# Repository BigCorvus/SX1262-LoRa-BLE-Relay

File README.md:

# SX1262-LoRa-BLE-Relay

These are multipurpose dev boards for the Semtech SX1262 chipset. EBYTE or CDSNET or whatever their name is sell multiple versions of RF modules based on this new LoRa chip on Aliexpress. One of its main advantages is the low RX current draw of about 5ma, which is that of the previous versions cut in half.  

This project can be used as a Relay between some BLE device and other LoRa nodes to implement a simple off-grid communicator or some day, as soon as LoRaWAN drivers for the SX1262 exist, it can connect to TTN. Probably the most interesting application: this device is planned to be used as hardware for the Meshtastic project https://github.com/meshtastic/Meshtastic-device  

Discussion: https://meshtastic.discourse.group/t/building-for-nrf52-boards/457/120  

These PCBs are designed for the SPI-versions of the LORA modules only (E22-900M30S which is the 1W version and E22-900M22S which transmits at 160mW max). Both operate in the 868 and 915Mhz band.  The MCU module is a cheap YJ-18010 by Holyiot which has an nRF52840, a ceramic antenna and low frequency crystal on board. The same module is also produced by Waveshare. It runs a Feather-nRF52840 bootloader and has roughly the same pinout, at least for UART, SPI and I2C. A tiny 160x80 IPS screen based on the ST7735 chipset and 3 buttons are provided for basic data visualisation and interfacing.  
When turned off the fuel gauge draws about 25-65µA. While turned on and in receive mode with the backlight off the 30dbm version draws about 18mA. The Backlight is additional 10mA depending on the current limiting resistor and PWM duty cycle. The smaller version draws only 9ma with bluetooth connected and in receive mode!! While transmitting the 30dbm version pulls about 1,2A from the battery!
Note that the 30dbm version of the board needs an extra 5V boost converter, which is a G5177C.  

A simple Arduino test sketch demonstrates the most important functions and can be used for communication already. It will be improved in the future.  

Update: v1.1 of the 30dbm as well as the 22dbm version is out. It has a simple slide switch and uses clickier buttons (LS12T2 from digikey). There's also a JST-SH 1mm connector for GPS modules and a high-side switch (generic SOT23 P-channel mosfet) controlled from P1.00 on the bigger board. LED2 has been moved to P1.10 and the LEDs rearranged. The boost converter is now controlled from P0.05 on the bigger board.

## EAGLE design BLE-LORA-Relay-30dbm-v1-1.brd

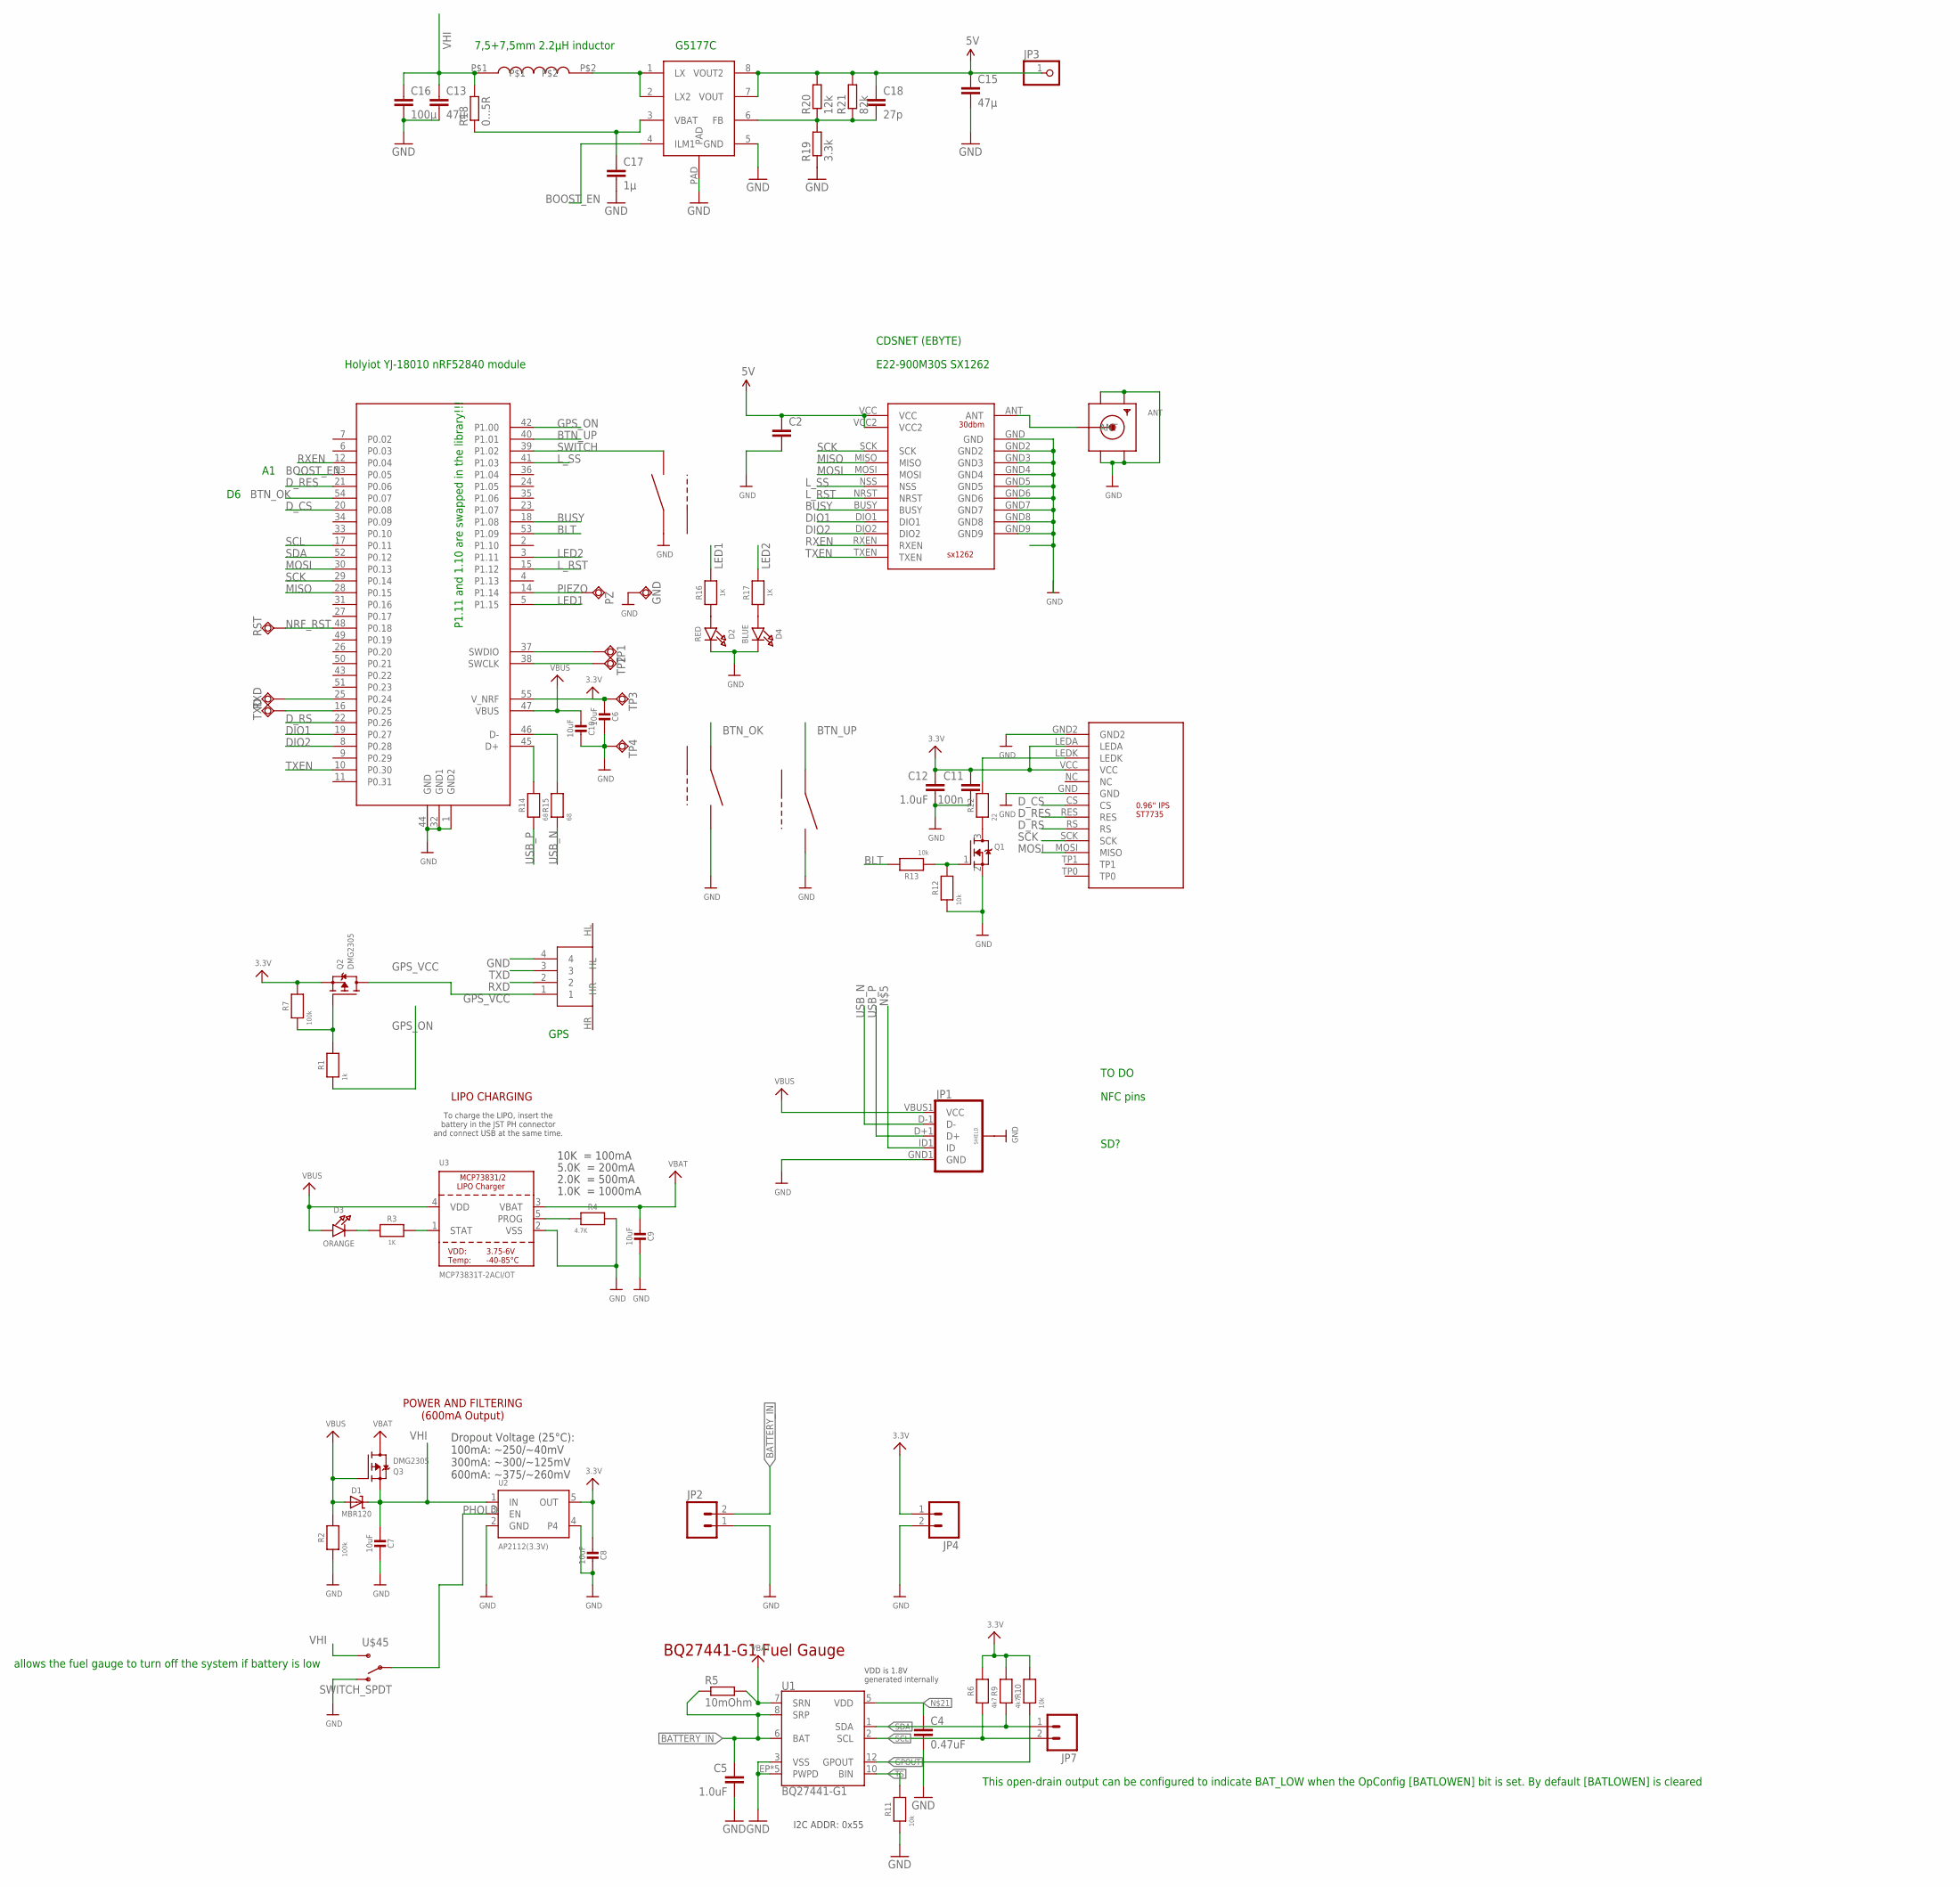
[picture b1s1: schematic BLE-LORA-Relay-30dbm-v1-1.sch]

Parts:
ANT: SMACONNECTOR_EDGE; SMA_EDGELAUNCH
C2: C-EUC1206; C1206
C4: 0.47uF; 0603-CAP
C5, C12: 1.0uF; 0603-CAP
C6, C7, C8, C9, C10: 10uF; 0805-NO
C11: 100n; 0603-CAP
C13, C15: 47µ; C0805
C16: 100µ; C1206
C17: 1µ; C0603
C18: 27p; C0603
D1: MBR120; SOD-123
D2: RED; CHIPLED_0805_NOOUTLINE
D3: ORANGE; CHIPLED_0805_NOOUTLINE
D4: BLUE; CHIPLED_0805_NOOUTLINE
DWN, DWN1, DWN2: LS12T2
GND: TPSQTP13R; TP13R
JP1: USB_MICROB_PLUGCONN-11752; USB-B-MICRO-SMD_V03
JP2, JP4, JP7: M02PTH; 1X02
JP3: PINHD-1X1; 1X01
PZ: TPSQTP13R; TP13R
Q1: MOSFET-NREFLOW; SOT23
Q2, Q3: DMG2305; SOT23-R
R1: 1k; 0603-NO
R2, R7: 100k; 0603-NO
R3, R16, R17: 1K; 0603-NO
R4: 4.7K; 0603-NO
R5: 10mOhm; R0805
R6, R9: 4k7; 0603-NO
R10, R11, R12, R13: 10k; 0603-NO
R14, R15: 68; 0603-NO
R18: 0...5R; R0603
R19: 3.3k; R0603
R20: 12k; R0603
R21: 82k; R0603
R22: 22; 0603-NO
RST: TPSQTP13R; TP13R
RXD: TPSQTP13R; TP13R
TP1, TP2, TP3, TP4: TPSQTP13R; TP13R
TXD: TPSQTP13R; TP13R
U1: BQ27441-G1; PDSO-N12
U2: AP2112(3.3V); SOT23-5
U3: MCP73831T-2ACI/OT; SOT23-5
U$14: NRF52840; NRF52840MOD
U$15: SX1262-30DBM
U$16: 0.96_IPS
U$17: JST-SH-3
U$35: 7.5MM-COIL; 7.5MM_COIL
U$41: G5177C; SO-08
U$45: SWITCH_SPDT; KPS-1290

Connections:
3.3V: C6.2, C8.2, C11.1, C12.1, JP4.1, Q2.2 (S), R6.2, R7.2, R9.2, R10.2, TP3.TP, U2.5 (OUT), U$14.55 (V_NRF), U$16.LEDA, U$16.VCC
5V: C2.1, C15.1, C18.1, JP3.1, R20.2, R21.2, U$15.VCC, U$15.VCC2, U$41.7 (VOUT), U$41.8 (VOUT2)
BATTERY_IN: C5.1, JP2.2, R5.1, U1.6 (BAT), U1.8 (SRP)
BLT: R13.2, U$14.53 (P1.09)
BOOST_EN: U$14.13 (P0.05), U$41.4 (ILM1)
BTN_OK: DWN.2, U$14.54 (P0.07)
BTN_UP: DWN1.2, U$14.40 (P1.01)
BUSY: U$14.18 (P1.08), U$15.BUSY
DIO1: U$14.19 (P0.27), U$15.DIO1
DIO2: U$14.8 (P0.28), U$15.DIO2
D_CS: U$14.20 (P0.08), U$16.CS
D_RES: U$14.21 (P0.06), U$16.RES
D_RS: U$14.22 (P0.26), U$16.RS
FB: C18.2, R19.2, R20.1, R21.1, U$41.6 (FB)
GND: ANT.GND@1 (GND4), ANT.GND@2 (GND3), ANT.GND@3 (GND2), ANT.GND@4 (GND1), C2.2, C4.2, C5.2, C6.1, C7.1, C8.1, C9.1, C10.1, C11.2, C12.2, C13.2, C15.2, C16.2, C17.2, D2.C, D4.C, DWN.1, DWN1.1, DWN2.2, GND.TP, JP1.GND1 (GND), JP1.SHIELD1 (SHIELD), JP1.SHIELD2 (SHIELD), JP1.SHIELD3 (SHIELD), JP2.1, JP4.2, Q1.2 (S), R2.1, R4.2, R11.1, R12.1, R19.1, TP4.TP, U1.3 (VSS), U1.EP (PWPD), U1.EP1 (PWPD), U1.EP2 (PWPD), U1.EP3 (PWPD), U1.EP4 (PWPD), U2.2 (GND), U2.4, U3.2 (VSS), U$14.1 (GND2), U$14.32 (GND1), U$14.44 (GND), U$15.GND, U$15.GND2, U$15.GND3, U$15.GND4, U$15.GND5, U$15.GND6, U$15.GND7, U$15.GND8, U$15.GND9, U$16.GND, U$16.GND2, U$17.4, U$41.5 (GND), U$41.PAD, U$45.O
GPOUT: R10.1, U1.12 (GPOUT)
GPS_ON: R1.1, U$14.42 (P1.00)
GPS_VCC: Q2.3 (D), U$17.1
LED1: R16.2, U$14.5 (P1.15)
LED2: R17.2, U$14.3 (P1.11)
L_RST: U$14.15 (P1.12), U$15.NRST
L_SS: U$14.41 (P1.03), U$15.NSS
MISO: U$14.28 (P0.15), U$15.MISO
MOSI: U$14.30 (P0.13), U$15.MOSI, U$16.MOSI (MISO)
unnamed: D3.C, R3.1
unnamed: Q1.1 (G), R12.2, R13.1
unnamed: ANT.P (ANT), U$15.ANT
unnamed: R22.2, U$16.LEDK
unnamed: R14.2, U$14.45 (D+)
unnamed: R15.2, U$14.46 (D-)
unnamed: Q2.1 (G), R1.2, R7.1
unnamed: R3.2, U3.1 (STAT)
unnamed: R4.1, U3.5 (PROG)
unnamed: D2.A, R16.1
unnamed: D4.A, R17.1
unnamed: Q1.3 (D), R22.1
unnamed: C17.1, R18.1, U$41.3 (VBAT)
unnamed: U$35.P$2, U$41.1 (LX), U$41.2 (LX2)
unnamed: C4.1, U1.5 (VDD)
NRF_RST: RST.TP, U$14.48 (P0.18)
PHOLD: U2.3 (EN), U$45.P
PIEZO: PZ.TP, U$14.14 (P1.14)
RXD: RXD.TP, U$14.25 (P0.24), U$17.2
RXEN: U$14.12 (P0.04), U$15.RXEN
SCK: U$14.29 (P0.14), U$15.SCK, U$16.SCK
SCL: JP7.2, R6.1, U1.2 (SCL), U$14.17 (P0.11)
SDA: JP7.1, R9.1, U1.1 (SDA), U$14.52 (P0.12)
SWCLK: TP2.TP, U$14.38 (SWCLK)
SWDIO: TP1.TP, U$14.37 (SWDIO)
SWITCH: DWN2.1, U$14.39 (P1.02)
TS: R11.2, U1.10 (BIN)
TXD: TXD.TP, U$14.16 (P0.25), U$17.3
TXEN: U$14.10 (P0.30), U$15.TXEN
USB_N: JP1.D-1 (D-), R15.1
USB_P: JP1.D+1 (D+), R14.1
VBAT: C9.2, Q3.3 (D), R5.2, U1.7 (SRN), U3.3 (VBAT)
VBUS: C10.2, D1.A, D3.A, JP1.VBUS1 (VCC), Q3.1 (G), R2.2, U3.4 (VDD), U$14.47 (VBUS)
VHI: C7.2, C13.1, C16.1, D1.C, Q3.2 (S), R18.2, U2.1 (IN), U$35.P$1, U$45.S

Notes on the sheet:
POWER AND FILTERING (600mA Output)
Dropout Voltage (25°C): 100mA: ~250/~40mV 300mA: ~300/~125mV 600mA: ~375/~260mV
10K = 100mA
5.0K = 200mA
2.0K = 500mA
1.0K = 1000mA
LIPO CHARGING
To charge the LIPO, insert the battery in the JST PH connector and connect USB at the same time.
BQ27441-G1 Fuel Gauge
VDD is 1.8V generated internally
I2C ADDR: 0x55
Holyiot YJ-18010 nRF52840 module
E22-900M30S SX1262
CDSNET (EBYTE)
7,5+7,5mm 2.2µH inductor
G5177C
P1.11 and 1.10 are swapped in the library!!!
GPS
allows the fuel gauge to turn off the system if battery is low
This open-drain output can be configured to indicate BAT_LOW when the OpConfig [BATLOWEN] bit is set. By default [BATLOWEN] is cleared
TO DO
NFC pins
SD?

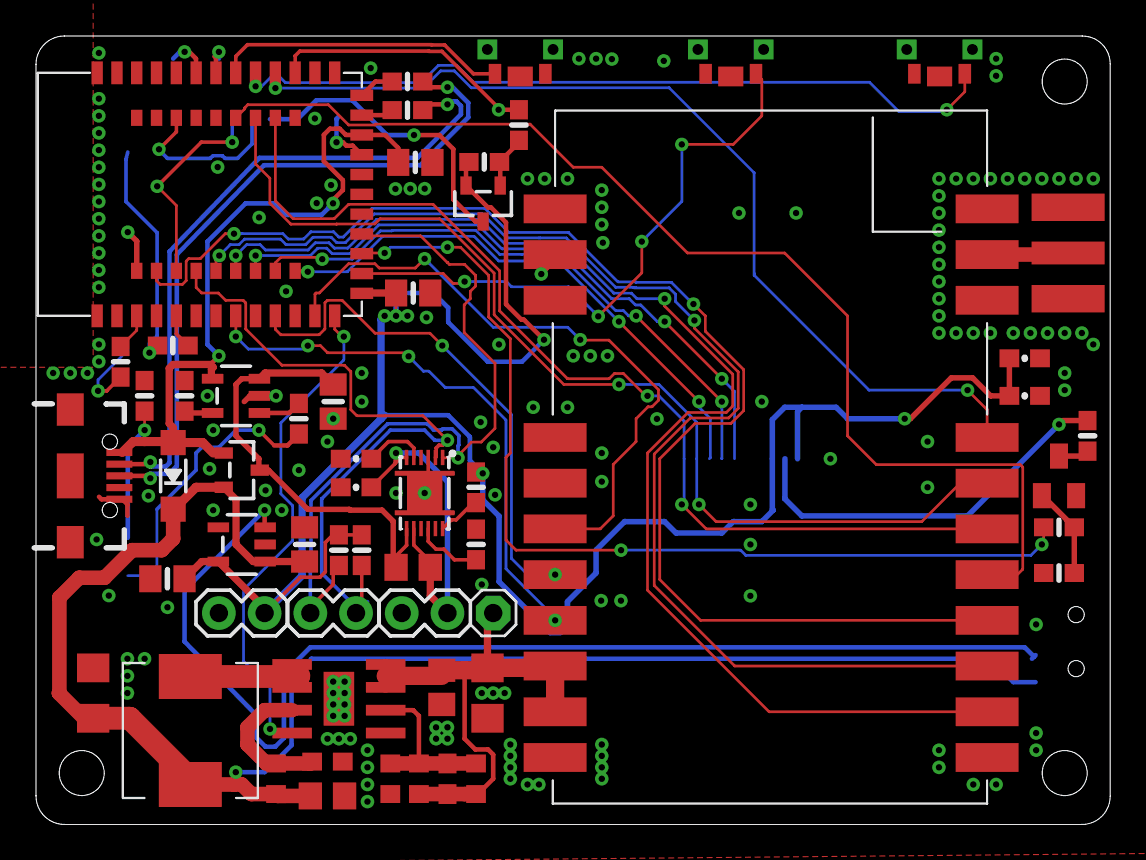
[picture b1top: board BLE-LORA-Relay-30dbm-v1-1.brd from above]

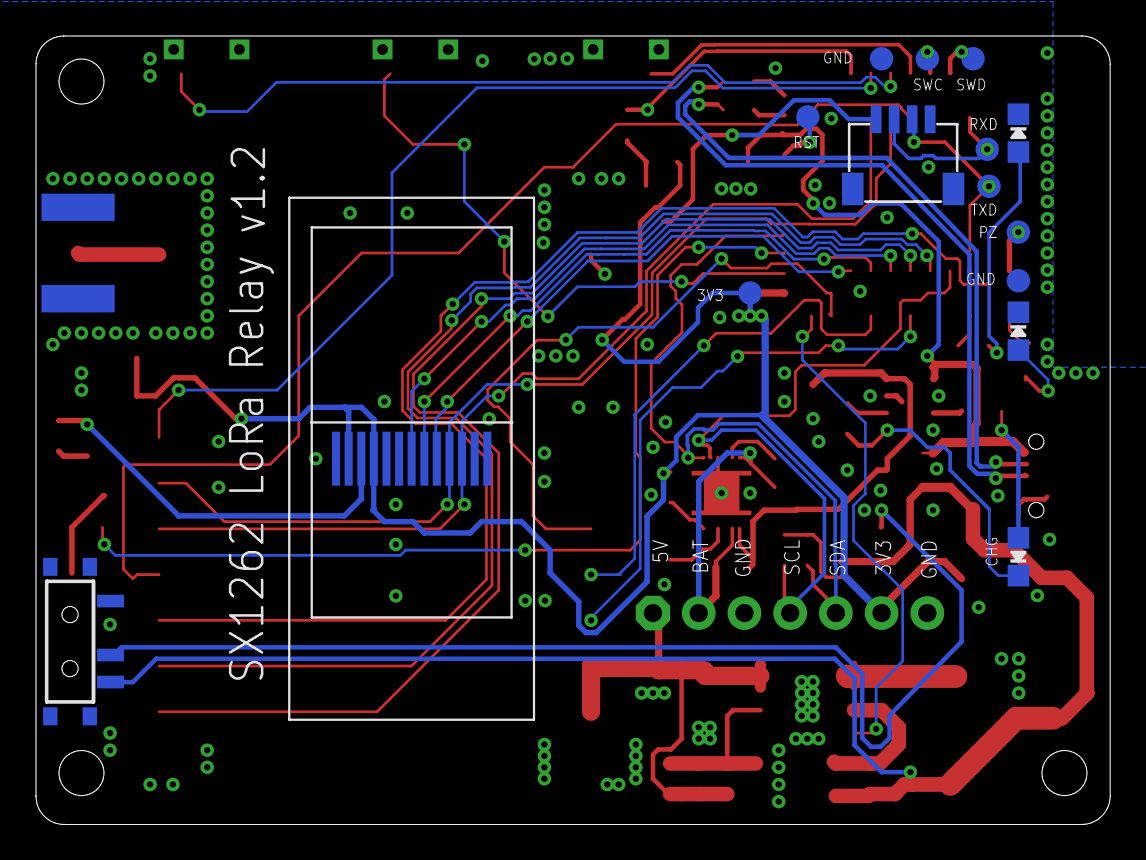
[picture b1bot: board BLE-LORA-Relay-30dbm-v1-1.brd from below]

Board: 2 copper layers, 59.7 x 43.8 mm, 71 parts (15 on the bottom side), 58 nets.

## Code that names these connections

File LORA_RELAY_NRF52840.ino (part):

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  Also implements all the housekeeping such as the BQ27441 fuel gauge, ST7735 LCD and buttons.
  If using the Feather nrf52840 express bootloader the SWITCH button can be used to enter bootloader mode if pressed on startup. LED1 is the bootloader LED
  Note that you need to modify the variant.h and variant.cpp as described below in order to get software acces to certain pins. See the core documentation for more info on where to find those files.
  Also note that the PHOLD pin was separated from the rest of the circuit by cutting a trace on the PCB between the P0.05 pad on the nrf52840 module and the via next to it so the power latching circuit is not used.
  This will be corrected in an upcoming version of the design files.

*********************************************************************/
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
*/
//the pin definitons are quite confusing, so watch out
#define DIO1 (10)//P0.27
#define DIO2 (17//P0.28
#define TXEN (16)//P0.30
#define RXEN (14)//P0.04
#define L_SS (39)//P1.03 -->35? actually 39
#define BUSY (5)//P1.08
#define L_RST (45)//P1.12 -->44? actually 45

#define BTN_TO_MCU (6)//P0.07
#define PHOLD (15)//P0.05
#define BTN_UP (38)//P1.01 -->33? actually 38
#define SWITCH (7)//P1.02

#define LED2 (44)//P1.11! actually wanted to connect it to 1.10 but made a mistake on the pcb, now it's on 1.11.
#define LED1 (4)//P1.15
#define PIEZO (47)//P1.14 -->46? actually 47

#define D_RES (11)//P0.06
#define D_CS (12)//P0.08
#define BLT (13)//P1.09
#define D_RS (9)//P0.26


// BLE Service
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
// SX1262 has the following connections:
// NSS pin:
// DIO1 pin:
// NRST pin:  <--? actually DIO2
// BUSY pin:

SX1262 lora = new Module(L_SS, DIO1, -1, BUSY);
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  setupBQ27441();
  soc = lipo.soc();  // Read state-of-charge (%)

  pinMode(LED1, OUTPUT);
  pinMode(LED2, OUTPUT);
  pinMode(BLT, OUTPUT);
  pinMode(L_RST, OUTPUT);
  pinMode(TXEN, OUTPUT);
  pinMode(RXEN, OUTPUT);

  pinMode(BTN_UP, INPUT_PULLUP);
  pinMode(SWITCH, INPUT_PULLUP);
  pinMode(BTN_TO_MCU, INPUT);
  //pinMode(PHOLD, INPUT); //PHOLD not used in my setup. I even cut its trace close to the nrf module and the EN pin of the LDO is pulled up ti VHI via regular spst switch

  digitalWrite(BLT, HIGH);
  digitalWrite(L_RST, LOW);
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

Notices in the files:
parts and their libraries:
microbuilder: This work is placed in the public domain, and may be freely used for commercial and non-commercial work with the following conditions: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
SparkFun-Connectors: Licensing: Creative Commons ShareAlike 4.0 International - https://creativecommons.org/licenses/by-sa/4.0
